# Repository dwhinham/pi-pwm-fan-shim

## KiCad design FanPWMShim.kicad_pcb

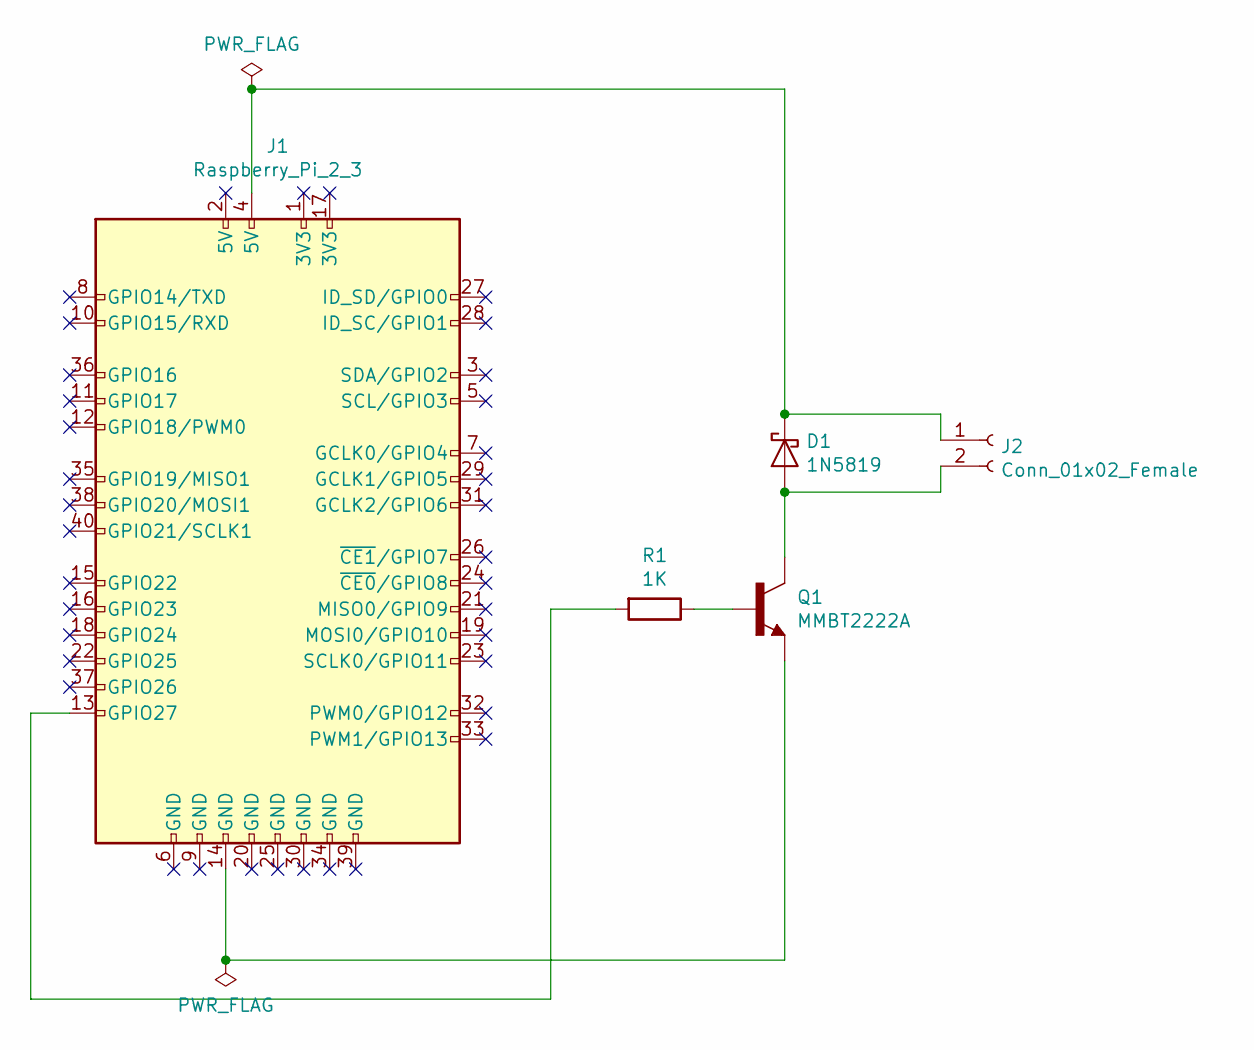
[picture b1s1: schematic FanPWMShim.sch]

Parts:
D1: 1N5819; D_SOD-123
J1: Raspberry_Pi_2_3; PinHeader_2x20_P2.54mm_Vertical
J2: Conn_01x02_Female; PinHeader_1x02_P2.00mm_Vertical
Q1: MMBT2222A; SOT-23
R1: 1K; R_0805_2012Metric

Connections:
unnamed: D1.1 (K), J1.4 (5V), J2.1
unnamed: D1.2 (A), J2.2, Q1.3 (C)
unnamed: J1.13 (GPIO27), R1.2
unnamed: J1.14 (GND), Q1.2 (E)
unnamed: Q1.1 (B), R1.1

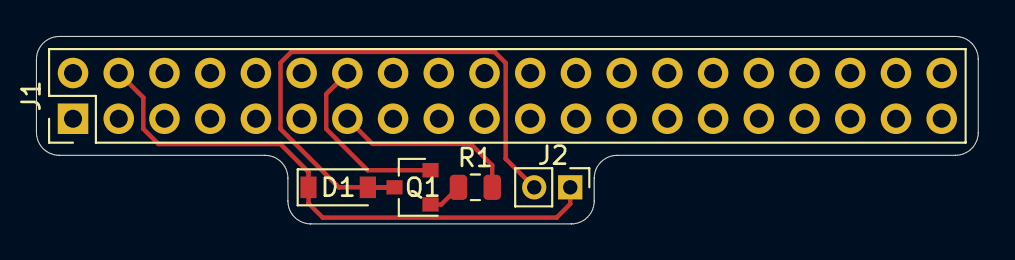
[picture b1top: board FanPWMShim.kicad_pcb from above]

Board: 2 copper layers, 52.3 x 10.4 mm, 5 parts (0 on the bottom side), 5 nets.

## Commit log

2019-08-01 Update PCB
